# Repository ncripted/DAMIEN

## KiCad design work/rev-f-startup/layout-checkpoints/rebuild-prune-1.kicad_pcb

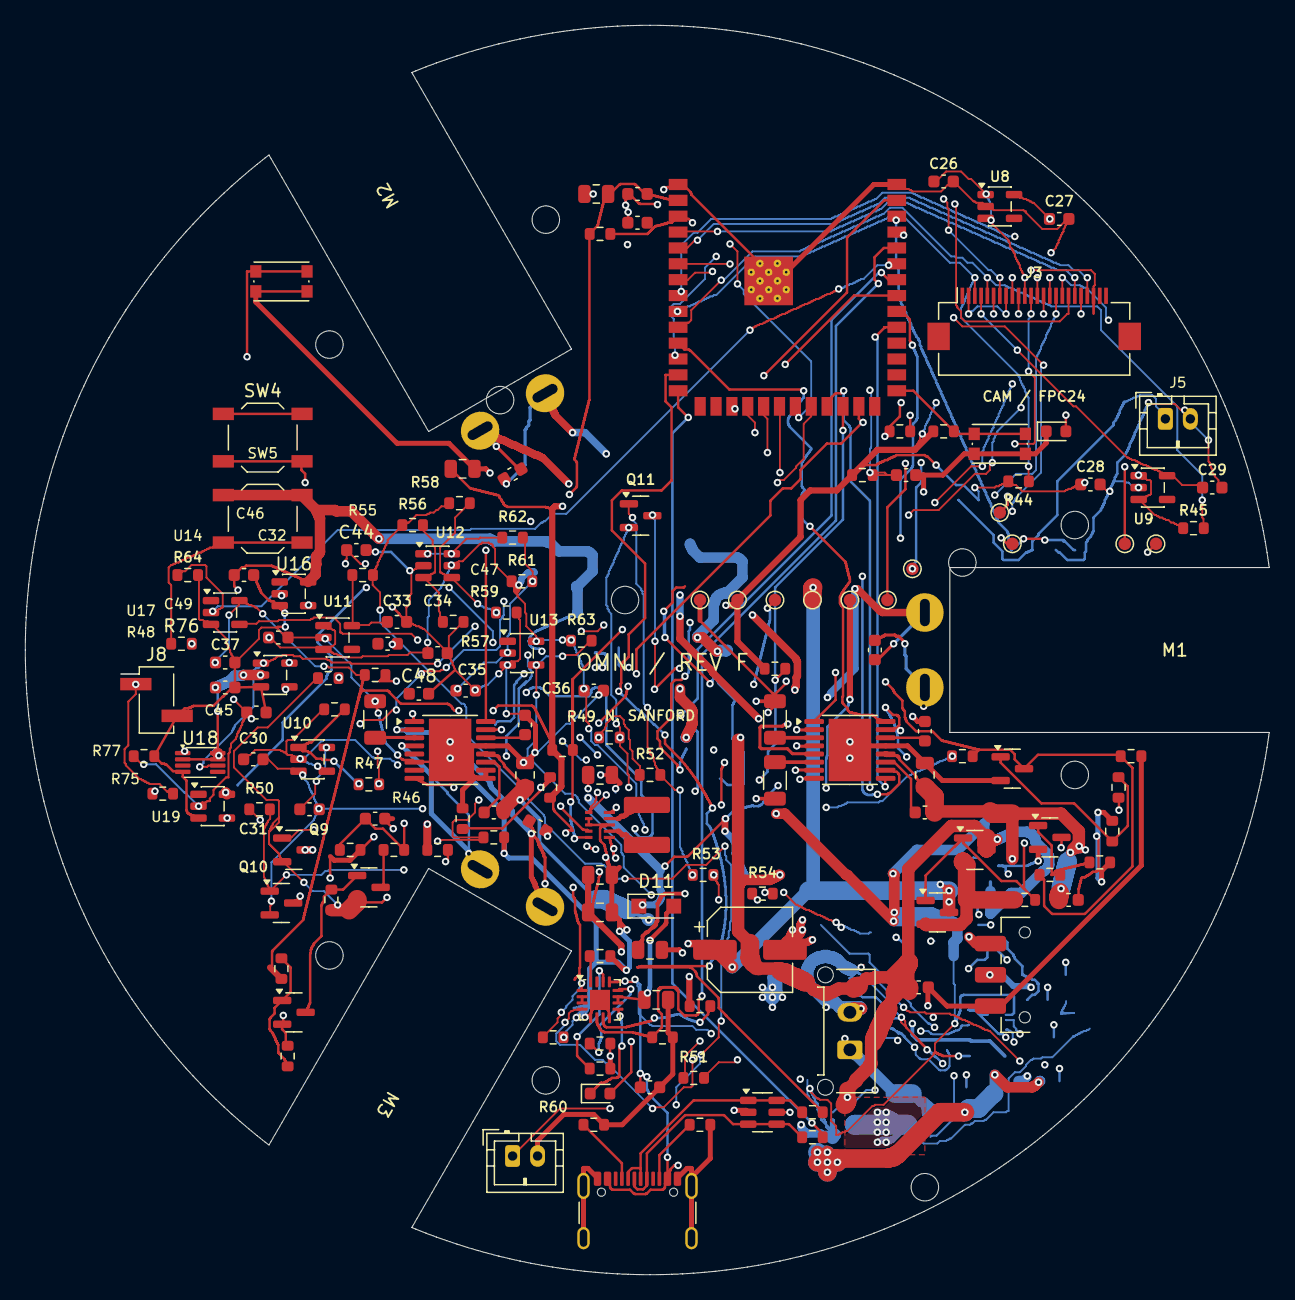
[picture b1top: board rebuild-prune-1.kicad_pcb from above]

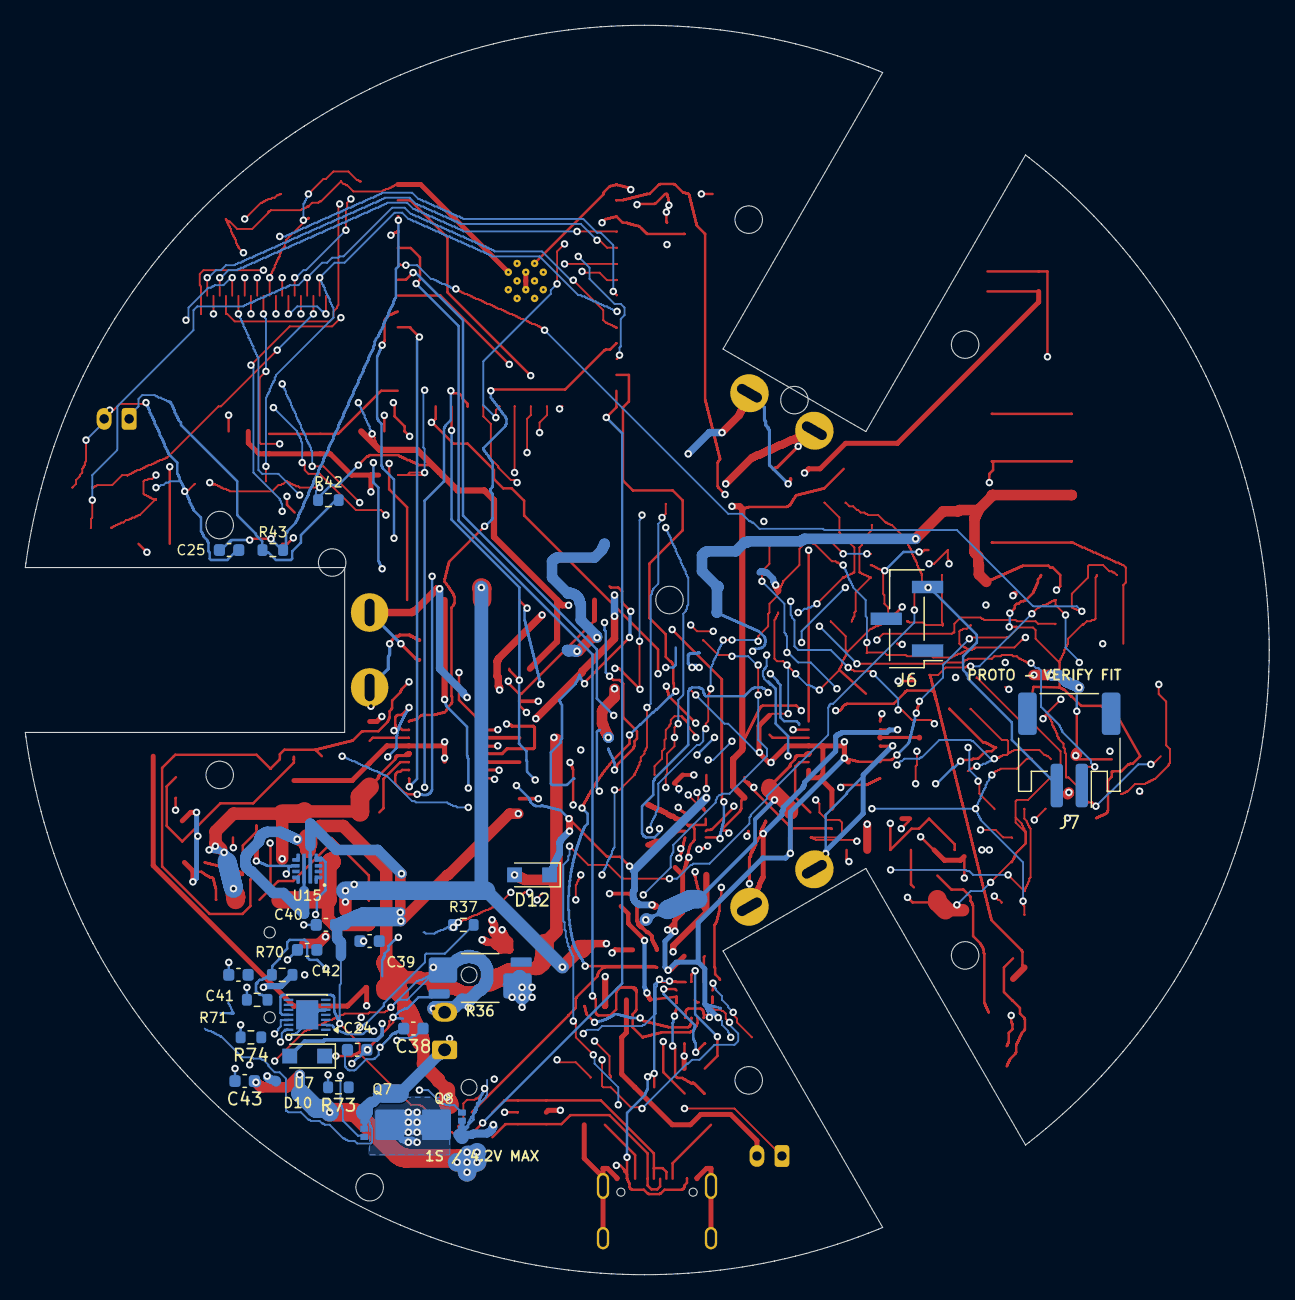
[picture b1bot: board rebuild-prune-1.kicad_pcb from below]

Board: 4 copper layers, 99.6 x 100.0 mm, 190 parts (24 on the bottom side), 123 nets.

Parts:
C1, C15, C21: 1u/10V; Capacitor_SMD__C_0603_1608Metric
C2, C5, C6, C9, C16, C17: 10u/10V; Capacitor_SMD__C_0805_2012Metric
C3, C4, C22, C23: 100n/16V; Capacitor_SMD__C_0603_1608Metric
C7, C10: 2.2u/10V; Capacitor_SMD__C_0603_1608Metric
C8, C11: 10n/25V; Capacitor_SMD__C_0603_1608Metric
C12, C13, C14: 100n/25V; Capacitor_SMD__C_0603_1608Metric
C18, C19, C20: 22u/10V X5R 20%; Capacitor_SMD__C_0805_2012Metric
C24: 100n X7R; Capacitor_SMD__C_0603_1608Metric
C25: 100n/16V X7R; Capacitor_SMD__C_0603_1608Metric
C26, C27, C28, C29, C32, C33: 2.2u/10V X7R; Capacitor_SMD__C_0603_1608Metric
C30, C31, C34, C36, C37: 100n/10V X7R; Capacitor_SMD__C_0603_1608Metric
C35: 220n/10V X7R; Capacitor_SMD__C_0603_1608Metric
C38, C44, C45, C46, C47, C48, C49: 100n X7R; C_0603_1608Metric
C39: 470n X7R; C_0603_1608Metric
C40: 2.2n 25V; C_0603_1608Metric
C41: 1n 16V; C_0603_1608Metric
C42: 100n 16V; C_0603_1608Metric
C43: 1u 16V; C_0603_1608Metric
C90: 220u/10V; CP_Elec_6.3x5.8_HandAssembly
D1: STATUS GREEN; LED_SMD__LED_0603_1608Metric
D2: CHARGE AMBER; LED_SMD__LED_0603_1608Metric
D10, D11, D12: PMEG3020ER; Nexperia_CFP3_SOD-123W
H1, H2, H3, H4, H5, H6, H7, H8, H9, H10: M2; MountingHole_2.2mm_M2
J1: USB-C; Connector_USB__USB_C_Receptacle_GCT_USB4105-xx-A_16P_TopMnt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
J2: RAW 1S CELL 4.2V MAX; Connector_Molex__Molex_Micro-Fit_3.0_43650-0215_1x02_P3.00m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
J3: M0031 CAMERA FPC24; Camera_FH12_24
J4: CELL NTC - CHARGER; Connector_JST__JST_PH_B2B-PH-K_1x02_P2.00mm_Vertical
J5: CELL NTC - DRIVE; Connector_JST__JST_PH_B2B-PH-K_1x02_P2.00mm_Vertical
J6: Fixture I2C; PinHeader_1x03_P2.54mm_Vertical_SMD_Pin1Left
J7: Cell NTC 10k; JST_PH_S2B-PH-SM4-TB_1x02-1MP_P2.00mm_Horizontal
J8: Open-drain fault input; PinHeader_1x02_P2.54mm_Vertical_SMD_Pin1Left
L1: 0.47uH/5.4A; L_XFL4015
M1: POLOLU 3065 MOTOR 1; Pololu_HPCB_Solder
M2: POLOLU 3065 MOTOR 2; Pololu_HPCB_Solder
M3: POLOLU 3065 MOTOR 3; Pololu_HPCB_Solder
Q1, Q2: DMP2035U-7; Package_TO_SOT_SMD__SOT-23
Q3, Q4, Q6, Q10, Q11: MMBT3904; Package_TO_SOT_SMD__SOT-23
Q5: AO3401A; Package_TO_SOT_SMD__SOT-23
Q7, Q8: CSD17308Q3; CSD17308Q3_TI
Q9: MMBT3906; Package_TO_SOT_SMD__SOT-23
R1, R2, R4, R5, R8, R29, R54: 10k; Resistor_SMD__R_0603_1608Metric
R3, R27, R62: 1k; Resistor_SMD__R_0603_1608Metric
R6, R7, R9: 0.25R/0.5W; Resistor_SMD__R_1206_3216Metric
R10, R11: 5.1k; Resistor_SMD__R_0603_1608Metric
R12, R13: 22R; Resistor_SMD__R_0603_1608Metric
R14: 3.57k; Resistor_SMD__R_0603_1608Metric
R15: 3.24k; Resistor_SMD__R_0603_1608Metric
R16: 46.4k; Resistor_SMD__R_0603_1608Metric
R17, R19, R22, R23, R26, R30, R31, R33, R34, R35, R46, R48, R61, R63, R64: 100k; Resistor_SMD__R_0603_1608Metric
R18: 2.2k; Resistor_SMD__R_0603_1608Metric
R20: 511k; Resistor_SMD__R_0603_1608Metric
R21: 91k; Resistor_SMD__R_0603_1608Metric
R24, R47: 22k; Resistor_SMD__R_0603_1608Metric
R25: 56k; Resistor_SMD__R_0603_1608Metric
R28, R49, R51, R53: 1M; Resistor_SMD__R_0603_1608Metric
R32: 47k; Resistor_SMD__R_0603_1608Metric
R36: 10m 1% Kelvin draft; WSK2512_T1p19_Kelvin
R37: 10R; Resistor_SMD__R_0603_1608Metric
R42, R55, R60: 10k 1%; Resistor_SMD__R_0603_1608Metric
R43: 1k 1%; Resistor_SMD__R_0603_1608Metric
R44, R45: 4.7k; Resistor_SMD__R_0603_1608Metric
R50: 33k; Resistor_SMD__R_0603_1608Metric
R52: 3.3k; Resistor_SMD__R_0603_1608Metric
R56: 200k 1%; Resistor_SMD__R_0603_1608Metric
R57, R59: 100k 1%; Resistor_SMD__R_0603_1608Metric
R58: 442k 1%; Resistor_SMD__R_0603_1608Metric
R70: 25.2k 0.1%; R_0603_1608Metric
R71: 10k 0.1%; R_0603_1608Metric
R73, R77: 100k; R_0603_1608Metric
R74: 750R 1%; R_0603_1608Metric
R75: 4.7k; R_0603_1608Metric
R76: 10k; R_0603_1608Metric
SW1: RESET; Button_Switch_SMD__SW_Push_1P1T_NO_CK_KMR2
SW2: BOOT; Button_Switch_SMD__SW_Push_1P1T_NO_CK_KMR2
SW3: POWER; Button_Switch_SMD__SW_SPDT_CK_JS102011SAQN
SW4: Momentary wake; SW_SPST_TL3342
SW5: Momentary rearm; SW_SPST_TL3342
TP1: GND; TestPoint__TestPoint_Pad_D1.0mm
TP2: +3V3; TestPoint__TestPoint_Pad_D1.0mm
TP3: VBAT; TestPoint__TestPoint_Pad_D1.0mm
TP4: VMOTOR; TestPoint__TestPoint_Pad_D1.0mm
TP5: SYS_RAW; TestPoint__TestPoint_Pad_D1.0mm
TP6: ESP_EN; TestPoint__TestPoint_Pad_D1.0mm
TP7: LED_STATUS; TestPoint__TestPoint_Pad_D1.0mm
TP8: DRIVE_ENABLE; TestPoint__TestPoint_Pad_D1.0mm
TP9: FAULT_U2; TestPoint__TestPoint_Pad_D1.0mm
TP10: FAULT_U3; TestPoint__TestPoint_Pad_D1.0mm
TP11: REG_PG; TestPoint__TestPoint_Pad_D1.0mm
U1: ESP32-S3-WROOM-1-N8R8; RF_Module__ESP32-S3-WROOM-1
U2, U3: DRV8833PWP; Package_SO__HTSSOP-16-1EP_4.4x5mm_P0.65mm_EP3.4x5mm_Mask2.4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
U4: TPS63802DLA; TPS63802_DLA0010A
U5: BQ24074RGT; Package_DFN_QFN__VQFN-16-1EP_3x3mm_P0.5mm_EP1.6x1.6mm
U6: USBLC6-2SC6; Package_TO_SOT_SMD__SOT-23-6
U7: MAX17301G+T; TDFN-14-1EP_3x3mm_P0.4mm_EP1.78x2.35mm
U8: TLV75513PDBVR; Camera_SOT23_5
U9: TLV75528PDBVR; Camera_SOT23_5
U10: TPS3840DL31DBVR; Camera_SOT23_5
U11: TLV75533PDBVR; Camera_SOT23_5
U12: TLV6700DDCR; Power_SOT23_6
U13: SN74LVC1G14DBVR; Camera_SOT23_5
U14: SN74LVC1G17DBVR; Camera_SOT23_5
U15: TPS259474LRPWR; TI_RPW0010A
U16: SN74LVC1G14DBVR; SOT-23-5
U17: TPS3840PL31DBVR; SOT-23-5
U18: SN74LVC1G74DCUR; VSSOP-8_2.3x2mm_P0.5mm
U19: SN74LVC1G17DBVR; SOT-23-5

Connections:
+3V3: C2.1, C3.1, C5.1, C19.1, C20.1, C26.1, C28.1, C37.1, J3.11, R1.1, R2.1, R4.1, R5.1, R8.1, R19.1, R20.1, R22.1, R32.1, R42.1, R44.1, R45.1, TP2.1, U1.2, U4.6, U8.1, U8.3, U9.1, U9.3, U14.5
ARM_CLK: U18.1, U19.4
ARM_CLR_N: U17.1, U18.6
ARM_FILTER: C45.1, R76.2, R77.1, U19.2
ARM_RESET_N: J8.1, R75.2, U17.4
ARM_SWITCH: R76.1, SW5.2
BATT_F: C24.1, C38.2, R37.2, U7.3
CAM_1V3: C27.1, J3.10, U8.5
CAM_2V8: C29.1, J3.4, U9.5
CAM_D0: J3.19, U1.4
CAM_D1: J3.21, U1.5
CAM_D2: J3.22, U1.6
CAM_D3: J3.20, U1.7
CAM_D4: J3.18, U1.12
CAM_D5: J3.16, U1.17
CAM_D6: J3.14, U1.18
CAM_D7: J3.12, U1.19
CAM_HREF: J3.9, U1.22
CAM_PCLK: J3.17, U1.20
CAM_RESET: C4.1, J3.6, R4.2
CAM_SCL: J3.5, R45.2, U1.10
CAM_SDA: J3.3, R44.2, U1.9
CAM_VSYNC: J3.7, U1.21
CAM_XCLK: J3.13, U1.8
CELL_CHG_TEMP: J4.1, R55.2, R56.1, R58.1
CELL_N: C30.2, C31.2, J2.2, Q10.2, Q11.2, R36.1, R49.2, R51.2, R53.2, U10.3
CELL_P: C30.1, J2.1, Q7.1, Q7.2, Q7.3, R37.1, R46.1, U10.2, U10.4
CELL_TEMP_ADC: C25.1, R43.2, U1.38
CELL_TEMP_DIV: J5.1, R42.2, R43.1
CELL_UV_CT: C31.1, U10.5
CELL_UV_EN_B: Q10.1, R50.2, R51.1
CELL_UV_FAULT: Q9.3, R49.1, R50.1, R52.1
CELL_UV_MOTOR_B: Q11.1, R52.2, R53.1
CELL_UV_PNP_B: Q9.1, R47.2, R48.2
CELL_UV_RESET_N: R46.2, R47.1, U10.1
CHG_3V3: C33.1, R55.1, U11.5
CHG_BAT: C16.1, D10.2, U5.2, U5.3
CHG_COLD_SENSE: R58.2, R59.1, U12.4
CHG_DISABLE: R63.2, U5.4, U13.4
CHG_HOT_SENSE: R56.2, R57.1, U12.3
CHG_ILIM: R15.1, U5.12
CHG_ISET: R14.1, U5.16
CHG_LED_A: D2.2, R18.2
CHG_OUT: C17.1, D11.2, U5.10, U5.11
CHG_PGOOD: R19.2, U5.7
CHG_STATUS: D2.1, U5.9
CHG_TEMP_ALLOW_RC: C35.1, R61.2, R62.2, U13.2
CHG_TEMP_OK_OD: R62.1, U12.1, U12.6
CHG_TIMER: R16.1, U5.14
CHG_TS_BIAS: R60.1, U5.1
CP: C38.1, U7.2
DRIVE_ENABLE: Q4.3, Q11.3, R25.1, R27.2, R28.1, TP8.1, U2.1, U3.1
DRIVE_REQ: R27.1, U14.4
DRIVE_REQ_RAW: R64.1, U1.35, U14.2
EF_EN: R73.1, U15.1, U18.5
EF_ILM: R74.1, U15.9
EF_SLEW: C40.1, U15.7
EF_TIMER: C41.1, U15.10
ESP_BOOT: R2.2, SW2.1, U1.27
ESP_EN: C1.1, R1.2, SW1.1, TP6.1, U1.3
FAULT_U2: R5.2, TP9.1, U1.24, U2.8
FAULT_U3: R8.2, TP10.1, U1.25, U3.8
GND: C1.2, C2.2, C3.2, C4.2, C5.2, C6.2, C7.2, C9.2, C10.2, C15.2, C16.2, C17.2, C18.2, C19.2, C20.2, C21.2, C22.2, C23.2, C25.2, C26.2, C27.2, C28.2, C29.2, C32.2, C33.2, C34.2, C35.2, C36.2, C37.2, C40.2, C41.2, C42.2, C43.2, C44.2, C45.2, C46.2, C47.2, C48.2, C49.2, C90.2, D1.1, J1.A1, J1.A12, J1.B1, J1.B12, J1.S1, J3.2, J3.8, J3.15, J4.2, J5.2, J8.2, Q3.2, Q4.2, Q6.2, R6.2, R7.2, R9.2, R10.2, R11.2, R14.2, R15.2, R16.2, R17.2, R21.2, R23.2, R26.2, R28.2, R30.2, R33.2, R35.2, R36.2, R57.2, R59.2, R60.2, R64.2, R71.2, R73.2, R74.2, R77.2, SW1.2, SW2.2, SW3.1, TP1.1, U1.1, U1.40, U1.41, U2.13, U2.17, U3.6, U3.9, U3.10, U3.13, U3.17, U4.2, U4.3, U4.8, U5.5, U5.8, U5.17, U6.2, U8.2, U9.2, U11.2, U12.2, U13.3, U14.3, U15.4, U15.8, U16.3, U17.3, U18.4, U19.3
LED_A: D1.2, R3.2
LED_STATUS: R3.1, TP7.1, U1.37
M1_A: C12.1, M1.1, U2.2
M1_B: C12.2, M1.2, U2.4
M1_IN1: U1.11, U2.16
M1_IN2: U1.23, U2.15
M1_SENSE: R6.1, U2.3
M2_A: C13.1, M2.1, U2.7
M2_B: C13.2, M2.2, U2.5
M2_IN1: U1.31, U2.9
M2_IN2: U1.32, U2.10
M2_SENSE: R7.1, U2.6
M3_A: C14.1, M3.1, U3.2
M3_B: C14.2, M3.2, U3.4
M3_IN1: U1.33, U3.16
M3_IN2: U1.34, U3.15
M3_SENSE: R9.1, U3.3
MEAS_BASE: Q6.1, R32.2, R33.1
MEAS_GATE: Q5.1, Q6.3, R31.2
MOTOR_BASE: Q3.1, R25.2, R26.1
MOTOR_GATE: Q1.1, Q2.1, Q3.3, R24.2
MOTOR_MID: Q1.2, Q2.2, R24.1
NTC_TH: J7.1, U7.1
PROG_SCL: J6.2, U7.9
PROG_SDA: J6.1, U7.8
PROTECTED_RAW: C42.1, C46.1, C47.1, C48.1, C49.1, D10.1, Q8.1, Q8.2, Q8.3, SW5.1, U7.11, U15.5, U16.5, U17.2, U18.2, U18.7, U18.8, U19.5
PROT_CHG: Q7.4, U7.14
PROT_CS_SENSE: R36.4, U7.6
PROT_DRAIN: Q7.5, Q7.6, Q7.7, Q7.8, Q7.9, Q8.5, Q8.6, Q8.7, Q8.8, Q8.9
PROT_DSG: Q8.4, U7.12
PROT_VSS_SENSE: C24.2, C39.2, J6.3, J7.2, R36.3, SW4.2, U7.5, U7.15
REG_1V8: C39.1, U7.7
REG_FB: R20.2, R21.1, U4.4
REG_L1: L1.1, U4.9
REG_L2: L1.2, U4.7
REG_PG: R22.2, TP11.1, U4.5
RESET_CT: C44.1, U17.5
SYS_ON: Q10.3, R23.1, R54.2, U4.1
SYS_ON_REQ: R54.1, SW3.2
SYS_RAW: C18.1, D11.1, D12.1, R18.1, SW3.3, TP5.1, U4.10
U2_VCP: C8.1, U2.11
U2_VINT: C7.1, U2.14
U3_VCP: C11.1, U3.11
U3_VINT: C10.1, U3.14
USB_5V: C15.1, C32.1, C34.1, C36.1, J1.A4, J1.A9, J1.B4, J1.B9, R29.1, R61.1, R63.1, R70.1, U5.13, U6.5, U11.1, U11.3, U12.5, U13.5, U16.2
USB_500_ENABLE: R17.1, U1.36, U5.6
USB_ABSENT: R75.1, U16.4
USB_CC1: J1.A5, R10.1
USB_CC2: J1.B5, R11.1
USB_DETECT_BASE: Q4.1, R29.2, R30.1
USB_DM: R12.2, U1.13
USB_DM_EXT: J1.A7, J1.B7, R12.1, U6.1, U6.6
USB_DP: R13.2, U1.14
USB_DP_EXT: J1.A6, J1.B6, R13.1, U6.3, U6.4
USB_INHIBIT: R70.2, R71.1, U15.2
VBAT: C21.1, C43.1, D12.2, Q1.3, Q5.2, Q9.2, R31.1, R48.1, TP3.1, U15.6
VBAT_ADC: C23.1, R34.2, R35.1, U1.39
VBAT_MEAS: Q5.3, R34.1
VMOTOR: C6.1, C8.2, C9.1, C11.2, C22.1, C90.1, Q2.3, TP4.1, U2.12, U3.12
WAKE: SW4.1, U7.10
